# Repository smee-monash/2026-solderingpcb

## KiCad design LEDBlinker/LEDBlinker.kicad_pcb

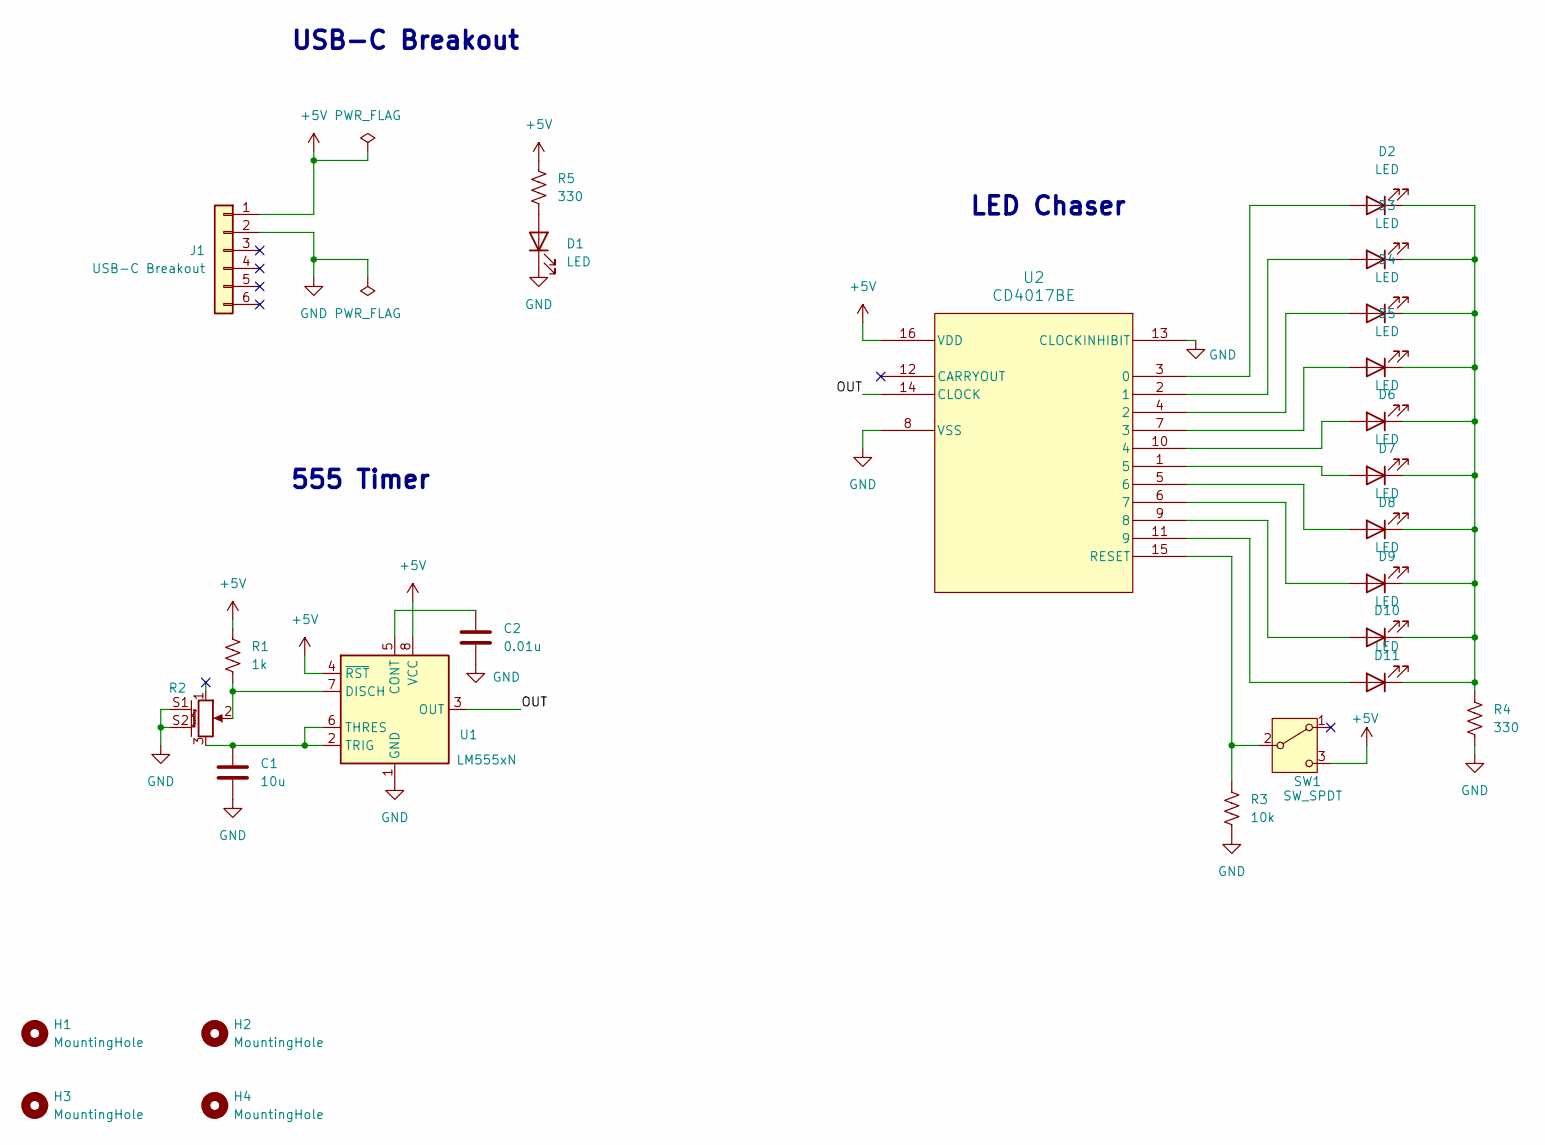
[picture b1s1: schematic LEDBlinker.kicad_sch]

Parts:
C1: 10u; CP_Radial_D5.0mm_P2.50mm
C2: 0.01u; C_Disc_D6.0mm_W4.4mm_P5.00mm
D1, D2, D3, D4, D5, D6, D7, D8, D9, D10, D11: LED; LED_D5.0mm_Clear
H1, H2, H3, H4: MountingHole; MountingHole_2.2mm_M2_DIN965
J1: USB-C Breakout; PinHeader_1x06_P2.54mm_Vertical
R1: 1k; R_Axial_DIN0207_L6.3mm_D2.5mm_P10.16mm_Horizontal
R2: PT01-D115D-B104; TRIM_PT01-D115D-B104; PARTREV 1.0
R3: 10k; R_Axial_DIN0207_L6.3mm_D2.5mm_P10.16mm_Horizontal
R4, R5: 330; R_Axial_DIN0207_L6.3mm_D2.5mm_P10.16mm_Horizontal
SW1: SW_SPDT; SW_SLW-883935-2A-D
U1: LM555xN; DIP-8_W7.62mm
U2: CD4017BE; N16

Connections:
+5V: J1.1, R1.1, R5.1, SW1.3 (C), U1.4 (~RST), U1.8 (VCC), U2.16 (VDD)
/OUT: U1.3 (OUT), U2.14 (CLOCK)
GND: C1.2, C2.2, D1.1 (K), J1.2, R2.S1 (MountPin), R2.S2 (MountPin), R3.1, R4.1, U1.1 (GND), U2.8 (VSS), U2.13 (CLOCKINHIBIT)
unnamed: D1.2 (A), R5.2
unnamed: D2.2 (A), U2.3 (0)
unnamed: D3.2 (A), U2.2 (1)
unnamed: D4.2 (A), U2.4 (2)
unnamed: D5.2 (A), U2.7 (3)
unnamed: D6.2 (A), U2.10 (4)
unnamed: D7.2 (A), U2.1 (5)
unnamed: D8.2 (A), U2.5 (6)
unnamed: D9.2 (A), U2.6 (7)
unnamed: D10.2 (A), U2.9 (8)
unnamed: D2.1 (K), D3.1 (K), D4.1 (K), D5.1 (K), D6.1 (K), D7.1 (K), D8.1 (K), D9.1 (K), D10.1 (K), D11.1 (K), R4.2
unnamed: D11.2 (A), U2.11 (9)
unnamed: R3.2, SW1.2 (B), U2.15 (RESET)
unnamed: C2.1, U1.5 (CONT)
unnamed: R1.2, R2.2, U1.7 (DISCH)
unnamed: C1.1, R2.3, U1.2 (TRIG), U1.6 (THRES)

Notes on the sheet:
USB-C Breakout
LED Chaser
555 Timer

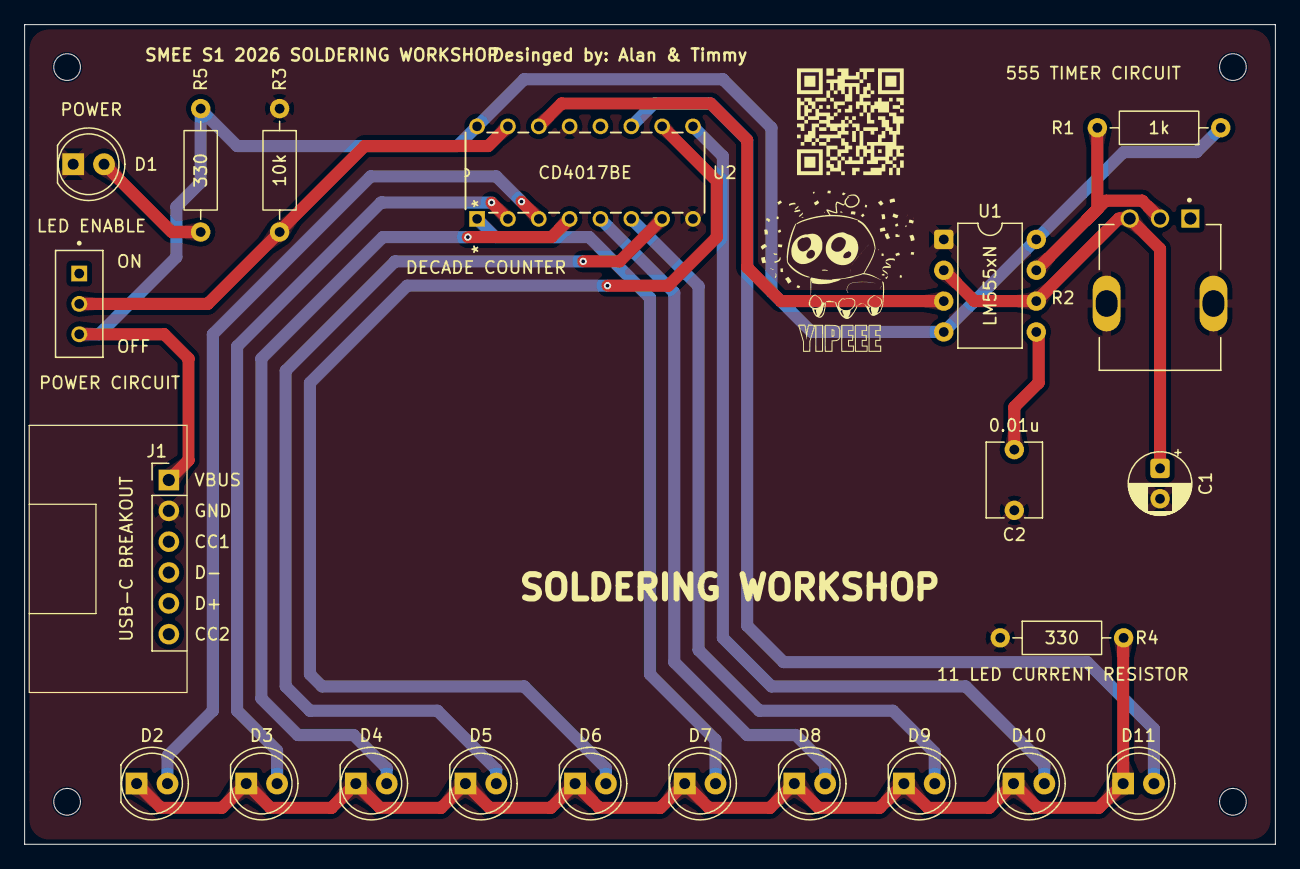
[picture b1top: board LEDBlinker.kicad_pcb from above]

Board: 2 copper layers, 103.0 x 67.5 mm, 26 parts (0 on the bottom side), 19 nets.

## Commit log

2026-05-01 Inital commit
2026-05-01 Created initial schematic for LED blinker
    includes IO, lights, switches, inversion and spot for timer
2026-05-03 Add KiCad PCB, parts, footprints and backups
    Add a full KiCad PCB file (LEDBlinker.kicad_pcb) with multiple LED footprints, mounting holes and models, and update related project files (.kicad_prl, .kicad_pro, .kicad_sch). Add several backup ZIP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
2026-05-03 Created PCB in shape of SMEE
2026-05-04 Added more space for components
2026-05-04 Add images/backups; update PCB footprint/logo
    Modify LEDBlinker.kicad_pcb: remove a zone_defaults line and replace/update a footprint (previous LED_THT entry replaced with a LOGO footprint), adjust properties (Reference/Value/Description/hide fl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
2026-05-05 Spaced out more
2026-05-05 Final commit before purchase
